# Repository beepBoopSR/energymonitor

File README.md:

# energyLink

**An AI home-energy monitor built for Surinamese households.**
team **beepBoop** · Hackomation 2026

energyLink clamps onto a home's main power line and continuously measures
consumption. For the first time, a household can watch its electricity bill build
in real time — in SRD, against the *actual* tiered EBS tariff — and get grounded,
practical advice in **Dutch and Sranan Tongo**, before the bill ever arrives.

---

## The problem it solves

- **The EBS household tariff is tiered.** The more you use, the more each next kWh
  costs — and the bill only arrives at the end of the cycle, as a surprise.
- **The grid is unstable.** Outages and brownouts are a daily reality.
- **Existing energy monitors don't fit Suriname.** They assume a stable grid, a flat
  tariff, and an English-speaking user, and none of them can tell you your EBS bill.

energyLink makes consumption, cost, and grid quality visible and predictable, in the
user's own language.

---

## What it does

- **Live power & live cost** — watts, volts, amps, and the cost *per hour* at the
  current draw, in SRD, updating in real time.
- **Accurate EBS billing** — tiered energy charge, per-phase basis fee, subsidy bands,
  and a bill prediction — all aligned to the household's EBS billing cycle, not the
  calendar month.
- **Tariff-band awareness** — shows where you sit across the tiers and how far to the
  next (more expensive) band.
- **Grid monitoring** — detects and logs outages and brownouts, with buffering so no
  data is lost when the power flickers.
- **AI advisory** — grounded, bilingual (Dutch + Sranan Tongo) advice based on the
  household's real measured data.
- **Appliance recognition** — a trained classifier identifies the *type* of the
  dominant load (resistive heater / motor / switching charger) from its current
  signature.
- **Per-circuit clamps** — support for naming and monitoring individual circuits.

---

## Architecture

```
  ESP32 + sensors            Node.js backend             Next.js frontend
  ───────────────            ───────────────             ────────────────
  ADS1115 (I²C)              POST /api/readings          polls /api/dashboard
  SCT-013 current   ──WiFi──▶  reconstruct time   ◀──HTTP──  every 5s, renders
  ZMPT101B voltage             store + analyse             live dashboard
                               SQL billing model
                                    │
                                    ▼
                               Supabase (Postgres)
```

- **Device → backend:** the ESP32 measures and POSTs readings; the backend
  reconstructs timestamps (handling offline buffering), stores them, and runs grid /
  anomaly / appliance checks on each reading.
- **Backend → frontend:** the frontend never talks to the device or database directly —
  it polls the backend's HTTP endpoints, which run the SQL billing model and return a
  single JSON payload.
- **Billing lives in the database** as data-driven SQL functions, so a tariff change is
  a data update, not a code change — and the same model serves the dashboard, the
  prediction, and the AI from one source of truth.

---

## Repository structure

```
energymonitor/
├── 3D-models hardware case/     3D model of an enclosure (designed but not used —
│                                 we bought an off-the-shelf case; kept for reference)
├── Back-end/                    Node.js + Express backend
│   ├── beepBoop-Back-End/       the runnable backend project (see below)
│   └── AI_training_appliance_models/   appliance-classifier training pipeline (see below)
├── C++ esp32 Firmwares/         ESP32 firmware — the full monitoring firmware, plus a
│                                 separate firmware used to capture waveforms for
│                                 appliance-fingerprint training
├── Extras/                      Business Model Canvas, poster, circuit diagram
├── SQL queries and functions/   Supabase schema, billing functions, seed data
├── api/                         API-related files
├── app/                         Next.js frontend (see below)
├── landingPage/                 Standalone marketing landing page
├── site/                        site assets
├── CLAUDE.md                    project notes
├── LICENSE
├── README.md                    this file
└── package.json
```

> The trees below list the **key files and their roles** — the important application
> code — rather than every file in the project. Config, generated, and dependency
> files are omitted for readability.

### Backend — `Back-end/beepBoop-Back-End/`

```
├── index.js                    Express app entry; registers routes, enables CORS
├── config/
│   └── supabase.js             configured Supabase client
├── routes/
│   ├── readings.js             POST /api/readings  ·  GET /api/dashboard
│   ├── tips.js                 GET /api/latest-tip  ·  POST /api/generate-tip
│   ├── settings.js             GET/POST /api/settings (phase, cycle, budget)
│   └── clamps.js               GET /api/clamps  ·  POST /api/clamps/rename
├── services/
│   ├── readings.js             reading ingestion + summary assembly
│   ├── reconstruction.js       timestamp reconstruction (offline buffering)
│   ├── gridMonitor.js          outage / brownout detection (with hysteresis)
│   ├── anomalyMonitor.js       power-spike + overuse detection
│   ├── applianceMonitor.js     appliance classifier — live inference
│   ├── energyContext.js        gathers the real context for the AI
│   ├── prompt.js               builds the grounded, bilingual AI prompt
│   ├── tips.js                 AI tip generation + retrieval
│   └── billPrediction.js       statistical bill projection (single source)
└── .env                        Supabase + Gemini keys (NOT committed)
```

### Appliance-classifier training — `Back-end/AI_training_appliance_models/`

```
├── 1_extract_features.py       waveform captures -> electrical features (CSV)
├── 2_train_model.py            train + cross-validate decision tree -> JSON
├── 3_inference_reference.js    reference of the JS inference (live in services/)
├── appliance_tree.json         the exported trained model
├── captures/                   example current-waveform captures
├── README.md                   pipeline documentation
└── NILM_future_work.md         why multi-appliance disaggregation was shelved
```

### Frontend — `app/app/`

```
├── app/
│   ├── page.tsx                redirects to /dashboard
│   ├── layout.tsx              sidebar shell (SidebarProvider)
│   ├── globals.css             energyLink light theme
│   ├── dashboard/page.tsx      main dashboard (live power, cost, tiers, AI, graphs)
│   ├── clamp/[id]/page.tsx     per-clamp detail (mini-dashboard + rename)
│   ├── uitval/page.tsx         outages (history)
│   ├── instellingen/page.tsx   settings (phase, EBS cycle, budget)
│   └── over/page.tsx           about / project story
├── components/
│   ├── app-sidebar.tsx         collapsible energyLink sidebar
│   ├── nav-main.tsx            nav items + active highlight
│   ├── nav-user.tsx            device identity footer
│   ├── clamps-section.tsx      dashboard Circuits section
│   └── ui/                     shadcn/ui components
├── lib/
│   └── api.ts                  API client, typed responses, mock data, USE_MOCK flag
├── next.config.ts
├── package.json
└── tsconfig.json
```

---

## Running it

Both the backend and the frontend must be running. The device (or synthetic data)
feeds the backend; the frontend polls the backend.

### Backend (port 3000)

```bash
cd Back-end
cd beepBoop-Back-End
node index.js
```

The backend serves on **port 3000** and exposes the API the frontend reads.

### Frontend (port 3001)

```bash
cd app
cd app
npm install          # first time only
npm run dev -- -p 3001
```

The frontend runs on **port 3001** (kept separate from the backend's 3000) and is
available at `http://localhost:3001`. Opening it redirects to the dashboard.

> The frontend fetches from the backend at `http://localhost:3000`. CORS is enabled on
> the backend so the cross-port requests are allowed. If the dashboard shows
> "kan geen verbinding maken," the backend isn't running or isn't reachable.

---

## Configuration

- **Backend:** environment variables for the Supabase connection and the AI (Gemini)
  API key live in the backend's environment (see the backend's own config). **Do not
  commit real keys.**
- **Frontend:** the API base URL and device id are set in the frontend's `lib/api.ts`.
  A `USE_MOCK` flag there switches between mock data and the live backend.
- **Database:** the SQL to create the schema, functions, and seed data is in
  `SQL queries and functions/` — run the table definitions first, then the functions,
  then the seed data.

---

## Firmware

The `C++ esp32 Firmwares/` folder contains two firmwares:

1. **Monitoring firmware** — the production firmware: samples voltage and current via
   the ADS1115, computes RMS/power/energy and waveform features, and POSTs readings to
   the backend over WiFi, with offline buffering and timestamp reconstruction.
2. **Fingerprint-capture firmware** — a separate build used during development to
   capture raw current waveforms of known appliances, for training the appliance
   classifier.

---

## Hardware

A sensing front-end around an ESP32:

- **ESP32 DevKit** — microcontroller with WiFi
- **ADS1115** — 16-bit I²C ADC (address 0x48; SDA→D21, SCL→D22)
- **SCT-013-000** — non-invasive current clamp, on the ADS1115 *differential* input
  A0–A1 with a 220 Ω burden resistor
- **ZMPT101B** — isolated AC voltage sensor, single-ended on A2

The circuit diagram is in `Extras/`. An enclosure 3D model is in
`3D-models hardware case/` (we used an off-the-shelf case in the end, but kept the
model).

---

## The AI, honestly scoped

energyLink uses AI in three distinct ways, and is deliberately precise about which is
which:

1. **Appliance recognition — trained machine learning.** A decision-tree classifier,
   trained on captured current waveforms, identifies the *type* of load from its
   electrical signature. (Training pipeline documented separately.)
2. **Advisory — a language model, grounded.** An LLM interprets the household's real
   computed data into personalized, bilingual advice, constrained so it never invents
   appliances or amounts.
3. **Anomaly detection — algorithmic.** Threshold-based spike and unusual-usage
   detection (not a trained model, and not described as one).

The **bill prediction is a transparent statistical projection, not AI** — we don't
dress it up as one. Multi-appliance disaggregation (NILM) was prototyped and shelved
for hardware reasons, documented as future work.

---

## Team

Built by team **beepBoop**, students at the Anton de Kom University of Suriname (ADeKUS),
for **Hackomation 2026**.

---

## License

See `LICENSE`.

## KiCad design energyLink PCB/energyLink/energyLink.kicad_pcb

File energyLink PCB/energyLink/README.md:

# energyLink — KiCad project (team beepBoop)

Home energy monitor for Suriname's grid (120–127 V, 60 Hz). Clamps the main
live conductor, measures consumption, buffers to ESP32 flash when WiFi is down,
and infers mains outages from its own power-loss timestamps.

## Files
| File | What it is |
|------|-----------|
| `energyLink.kicad_sch` | Schematic — all components with net-label connectivity |
| `energyLink.kicad_pcb` | PCB — 55×40 mm outline, isolation slot, zoned placement |
| `energyLink.net`       | Netlist — importable into Pcbnew if needed |
| `energyLink.kicad_pro` | Project file — open this in KiCad first |

Open `energyLink.kicad_pro` in KiCad 7 or 8.

## Please read — these files were generated programmatically
They are structurally valid and parse cleanly, but they were built without the
KiCad GUI, so treat them as a strong starting point, not a finished board:

1. Symbols are simple labelled rectangles with correct pins and nets. On first
   open, run **Inspect → Electrical Rules Check (ERC)**. Connectivity is carried
   by net labels on each pin, which is valid but will raise a few "no power flag"
   ERC notes — add PWR_FLAG on +3V3 / +5V / GND to clear them.
2. Footprints are named to standard KiCad libraries (`Converter_ACDC`,
   `RF_Module`, etc.). If a name doesn't resolve on your install, reassign via
   **Tools → Footprint Assignment**. The `.kicad_pcb` uses simplified 2-pad
   placeholders so you can see the zoned layout; swap in the real footprints
   before routing.
3. The PCB shows **placement and the isolation strategy**, not routed copper.
   Route it in Pcbnew — keep every mains trace inside the left zone.

## Design summary
- **Isolated SELV logic.** The only mains-referenced parts are J3, F1, RV1, the
  HLK-PM01 primary, and the ZMPT101B primary. CT, ZMPT, and HLK all isolate, so
  the ESP32/ADS1115 ground never touches mains — which is what makes the
  external 3.5 mm CT jack safe to handle.
- **Current:** SCT-013-000 → 3.5 mm jack → 22 Ω burden across ADS1115 A0–A1,
  biased to ~1.65 V via the VMID divider (R2/R3/Cb).
- **Voltage:** ZMPT101B isolated output → ADS1115 A2 (VSENSE).
- **Power:** HLK-PM01 (mains→5 V) → AMS1117-3.3 → 3V3. C1 470 µF bulk at the
  ESP32 prevents WiFi brownout resets.
- **Safety:** fuse + MOV on the line input; ≥6–8 mm creepage and a milled slot
  between mains and SELV zones (CAT III near a panel). A real product needs
  proper safety testing/certification and, in most places, electrician install.

## Productization notes (not in these files)
- Consider replacing the ADS1115 with an **ADE7953** metering IC for true active
  power / power factor (the ADS1115 multiplexes, so V and I aren't sampled
  simultaneously). Keep it inside the isolated domain, fed from the ZMPT output.
- **ESP32-C3-MINI-1** is smaller/cheaper and plenty for this workload.

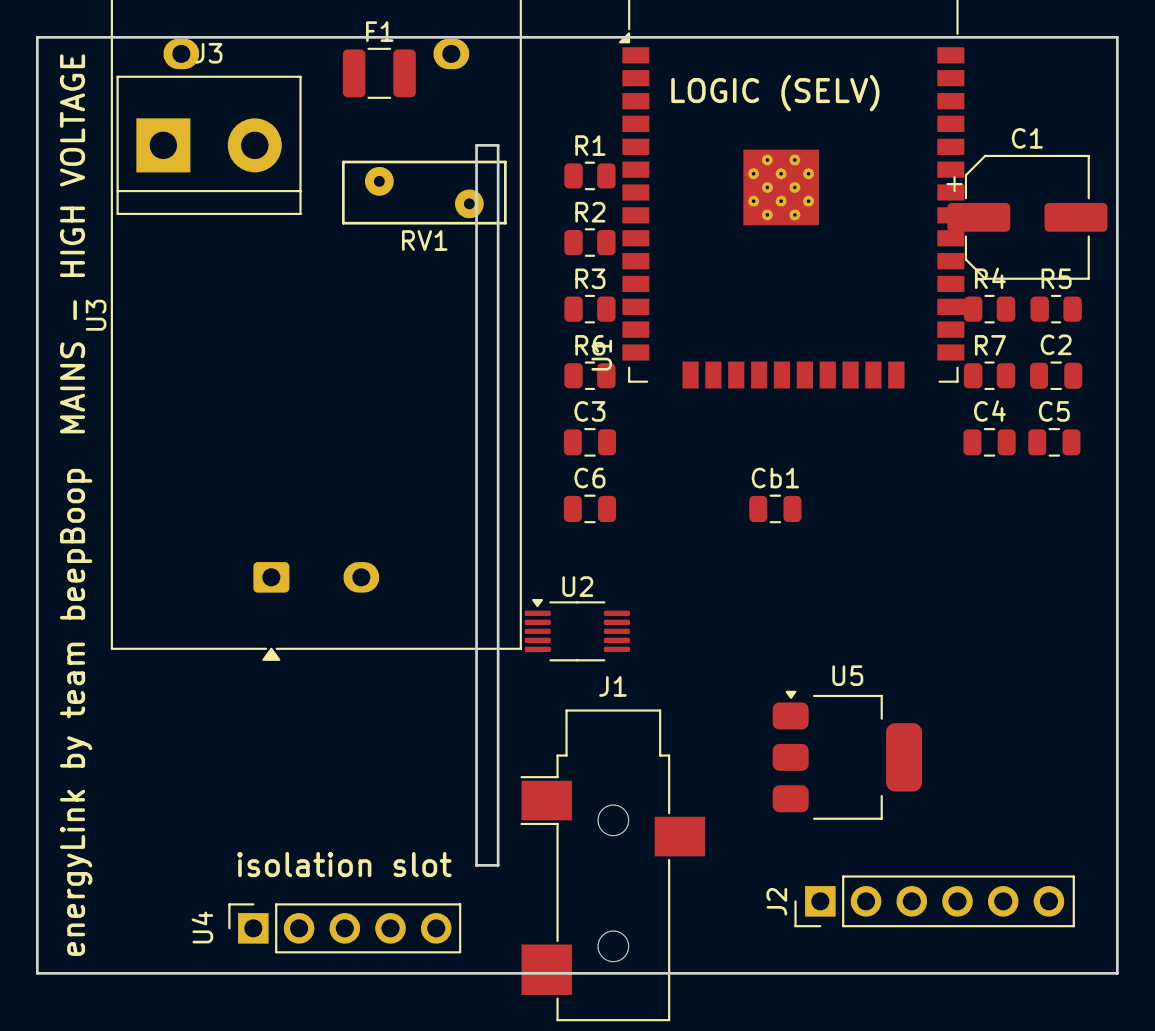
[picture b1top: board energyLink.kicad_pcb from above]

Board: 2 copper layers, 60.0 x 52.0 mm, 24 parts (0 on the bottom side), 15 nets, no tracks yet.

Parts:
C1: 470uF_bulk; CP_Elec_6.3x7.7
C2, C3, C6: 100nF; C_0805_2012Metric
C4, C5: 10uF; C_0805_2012Metric
Cb1: 10uF_bias; C_0805_2012Metric
F1: Fuse_500mA_slow; Fuse_1210_3225Metric
J1: 3.5mm_CT_jack; Jack_3.5mm_CUI_SJ-3523-SMT_Horizontal
J2: Prog_1x6; PinHeader_1x06_P2.54mm_Vertical
J3: Mains_1x2; TerminalBlock_bornier-2_P5.08mm
R1: 22R_burden; R_0805_2012Metric
R2, R3: 100k; R_0805_2012Metric
R4: 4k7_SDA; R_0805_2012Metric
R5: 4k7_SCL; R_0805_2012Metric
R6: 10k_EN; R_0805_2012Metric
R7: 10k_IO0; R_0805_2012Metric
RV1: MOV_150VAC; RV_Disc_D9mm_W3.4mm_P5mm
U1: ESP32-WROOM-32
U2: ADS1115; VSSOP-10_3x3mm_P0.5mm
U3: HLK-PM01; Converter_ACDC_Hi-Link_HLK-PMxx
U4: ZMPT101B; PinSocket_1x05_P2.54mm_Vertical
U5: AMS1117-3.3; SOT-223-3_TabPin2

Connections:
/+3V3: C1.1, C2.1, C3.1, C5.1, J2.2 (3V3), R2.1, R4.2, R5.2, R6.2, R7.2, U1.1 (3V3), U2.1 (VDD), U4.3 (VCC), U5.3 (VOUT)
/+5V: C4.1, C6.1, U3.3 (+Vo), U5.1 (VIN)
/CT_A0: R1.1, U2.6 (A0)
/EN: J2.3 (EN), R6.1, U1.3 (EN)
/GND: C1.2, C2.2, C3.2, C4.2, C5.2, C6.2, Cb1.2, J2.1 (GND), R3.2, U1.2 (GND), U2.2 (GND), U2.5 (ADDR), U3.4 (-Vo), U4.5 (GND), U5.2 (GND)
/IO0: J2.4 (IO0), R7.1, U1.4 (IO0)
/L_FUSED: F1.2, RV1.1, U3.1 (L), U4.1
/L_IN: F1.1, J3.1 (L)
/N_MAINS: J3.2 (N), RV1.2, U3.2 (N), U4.2
/RX: J2.6 (RX), U1.8 (RXD0)
/SCL: R5.1, U1.6 (IO22_SCL), U2.3 (SCL)
/SDA: R4.1, U1.5 (IO21_SDA), U2.4 (SDA)
/TX: J2.5 (TX), U1.7 (TXD0)
/VMID: Cb1.1, R1.2, R2.2, R3.1, U2.7 (A1)
/VSENSE: U2.8 (A2), U4.4 (OUT)

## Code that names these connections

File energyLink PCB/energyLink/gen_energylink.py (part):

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               ("8","A2","VSENSE","R"),("9","A3","NC","R")]),
    dict(ref="U3", value="HLK-PM01", fp="Converter_ACDC:Converter_ACDC_HLK-PMxx",
         sym="HLK_PM01",
         pins=[("1","L","L_FUSED","L"),("2","N","N_MAINS","L"),
               ("3","+Vo","+5V","R"),("4","-Vo","GND","R")]),
    dict(ref="U4", value="ZMPT101B", fp="Transformer_THT:Transformer_ZMPT101B",
         sym="ZMPT101B",
         pins=[("1","P1","L_FUSED","L"),("2","P2","N_MAINS","L"),
               ("3","VCC","+3V3","R"),("4","OUT","VSENSE","R"),("5","GND","GND","R")]),
    dict(ref="U5", value="AMS1117-3.3", fp="Package_TO_SOT_SMD:SOT-223-3_TabPin2",
         sym="AMS1117_33",
         pins=[("1","VIN","+5V","L"),("2","GND","GND","L"),("3","VOUT","+3V3","R")]),
    dict(ref="J1", value="3.5mm_CT_jack", fp="Connector_Audio:Jack_3.5mm_CUI_SJ1-3533N",
         sym="JACK_CT",
         pins=[("1","TIP","CT_A0","L"),("2","SLEEVE","VMID","L")]),
    dict(ref="J2", value="Prog_1x6", fp="Connector_PinHeader_2.54mm:PinHeader_1x06_P2.54mm_Vertical",
         sym="HDR_PROG",
         pins=[("1","GND","GND","R"),("2","3V3","+3V3","R"),("3","EN","EN","R"),
               ("4","IO0","IO0","R"),("5","TX","TX","R"),("6","RX","RX","R")]),
    dict(ref="J3", value="Mains_1x2", fp="TerminalBlock:TerminalBlock_bornier-2_P5.08mm",
         sym="TERM_MAINS",
         pins=[("1","L","L_IN","L"),("2","N","N_MAINS","L")]),
    dict(ref="F1", value="Fuse_500mA_slow", fp="Fuse:Fuse_1210_3225Metric",
         sym="FUSE", pins=[("1","1","L_IN","L"),("2","2","L_FUSED","R")]),
    dict(ref="RV1", value="MOV_150VAC", fp="Varistor:RV_Disc_D9mm_W3.4mm_P5mm",
         sym="MOV", pins=[("1","1","L_FUSED","L"),("2","2","N_MAINS","R")]),
    dict(ref="R1", value="22R_burden", fp="Resistor_SMD:R_0805_2012Metric",
         sym="R", pins=[("1","1","CT_A0","L"),("2","2","VMID","R")]),
    dict(ref="R2", value="100k", fp="Resistor_SMD:R_0805_2012Metric",
         sym="R", pins=[("1","1","+3V3","L"),("2","2","VMID","R")]),
    dict(ref="R3", value="100k", fp="Resistor_SMD:R_0805_2012Metric",
         sym="R", pins=[("1","1","VMID","L"),("2","2","GND","R")]),
    dict(ref="R4", value="4k7_SDA", fp="Resistor_SMD:R_0805_2012Metric",
         sym="R", pins=[("1","1","SDA","L"),("2","2","+3V3","R")]),
    dict(ref="R5", value="4k7_SCL", fp="Resistor_SMD:R_0805_2012Metric",
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    dict(ref="C6", value="100nF", fp="Capacitor_SMD:C_0805_2012Metric",
         sym="C", pins=[("1","1","+5V","L"),("2","2","GND","R")]),
    dict(ref="Cb", value="10uF_bias", fp="Capacitor_SMD:C_0805_2012Metric",
         sym="C", pins=[("1","1","VMID","L"),("2","2","GND","R")]),
]

# unique symbol geometry
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
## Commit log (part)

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2026-06-28 scaffolding
2026-06-28 App basic shadcn setup
    Add shadcn/sidebar setup steps and a quick run command to README (cd app; npx shadcn@latest add sidebar-07; npm run dev --prefix app). Also add license entries to package-lock.json for the root (MIT)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
2026-06-28 add app
